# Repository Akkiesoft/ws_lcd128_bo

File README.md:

# Breakout boards for WaveShare RP2040-LCD-1.28

WaveShare RP2040-LCD-1.28のGPIOポートを利用した各種基板データ置き場です。

[GPIOの配置などはWaveShareのWikiを参照してください。](https://www.waveshare.com/wiki/RP2040-LCD-1.28)

* データ作成環境
    * KiCad 9.0.4
* 基板発注方法
    * のにそちしで基板のガーバーデータ、ドリルデータを生成します
    * JLCPCBなどで発注します
        * 基板の厚みは1.2mm程度もあれば十分です

## ブレイクアウトボード(board-breakout)

1.27mmピッチのGPIOピンを2.54mmピットに変換するブレイクアウトです。適当に空けた2.6mmの穴3つ付き。

基板1枚あたりに必要な部材は以下のとおりです。

* このデータから作成した基板 1枚
* 2x10 1.27mmピンヘッダー 2つ
* 2x10 2.54mmピンヘッダーもしくはピンソケット 2つ

## WIZnetチップ搭載Ethernetモジュール変換ボード(board-w5500)

RP2040-LCD-1.28にWIZnetチップ搭載Ethernetモジュールを搭載するための変換ボードです。

基板1枚あたりに必要な部材は以下のとおりです。

* このデータから作成した基板 1枚
* 2x10 1.27mmピンヘッダー 2つ
* WIZnetチップ搭載Ethernetモジュール
* お好みでロープロファイルピンヘッダー・ピンソケットの1x6を2つずつ
    * Ethernetモジュールのピンヘッダーは除去して付け替えます
    * 全体高を減らせます

GPIO配置は以下のとおりです。

* GP16: MI
* GP17: CSn
* GP18: SCK
* GP19: MO
* GP20: RST

## ライセンス / License

MIT License

2025 Akkiesoft

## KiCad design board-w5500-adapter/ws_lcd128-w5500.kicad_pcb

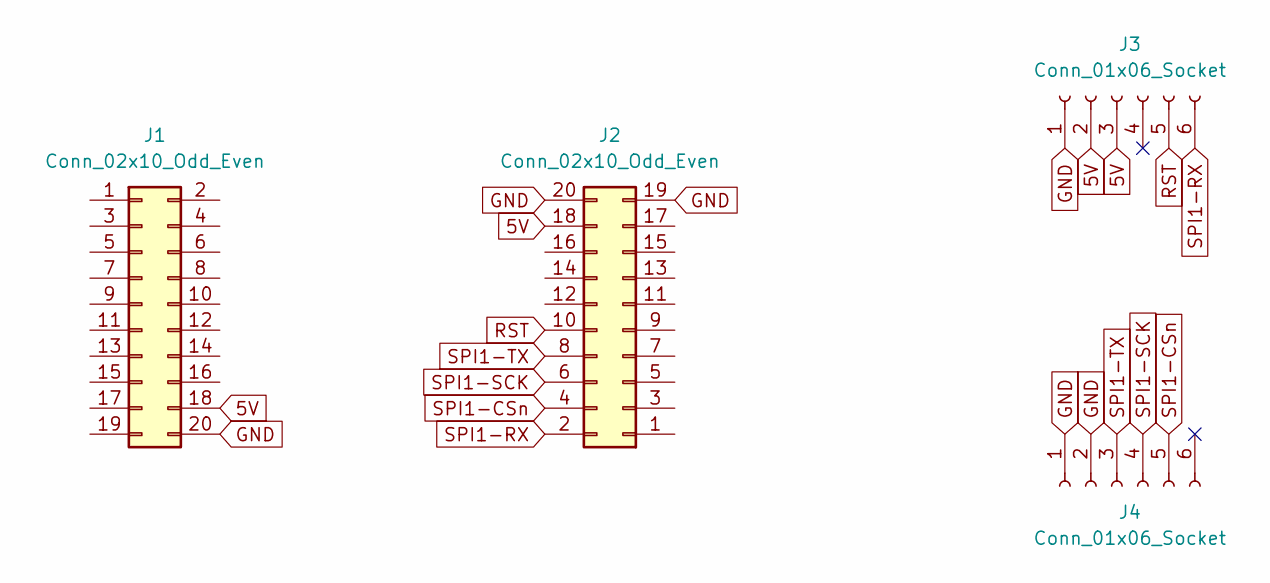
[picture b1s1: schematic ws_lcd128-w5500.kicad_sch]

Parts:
J1, J2: Conn_02x10_Odd_Even; PinHeader_2x10_P1.27mm_Vertical
J3, J4: Conn_01x06_Socket; PinHeader_1x06_P2.54mm_Vertical

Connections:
5V: J1.18, J2.18, J3.2, J3.3
GND: J1.20, J2.19, J2.20, J3.1, J4.1, J4.2
RST: J2.10, J3.5
SPI1-CSn: J2.4, J4.5
SPI1-RX: J2.2, J3.6
SPI1-SCK: J2.6, J4.4
SPI1-TX: J2.8, J4.3

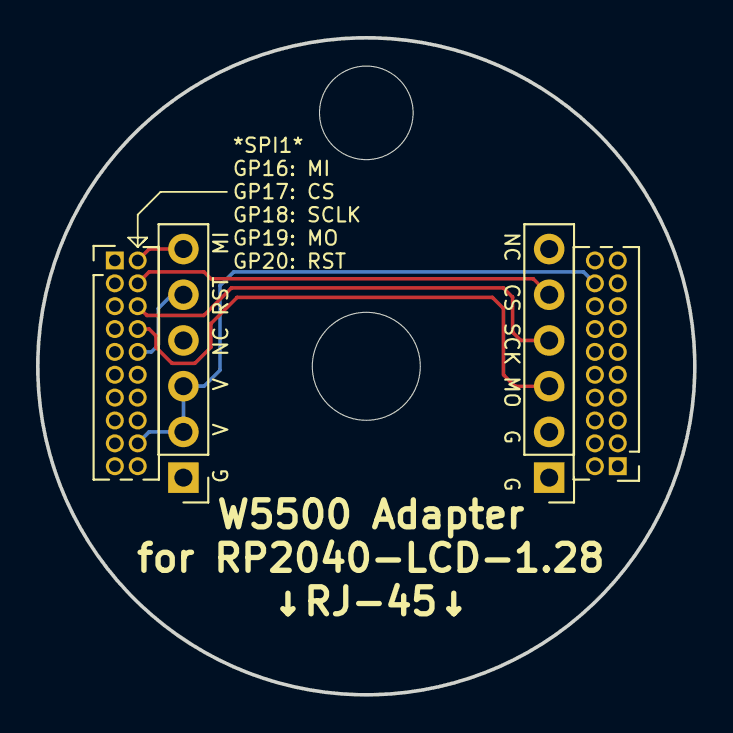
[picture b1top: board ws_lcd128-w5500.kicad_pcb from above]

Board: 2 copper layers, 36.5 x 36.5 mm, 4 parts (0 on the bottom side), 7 nets.

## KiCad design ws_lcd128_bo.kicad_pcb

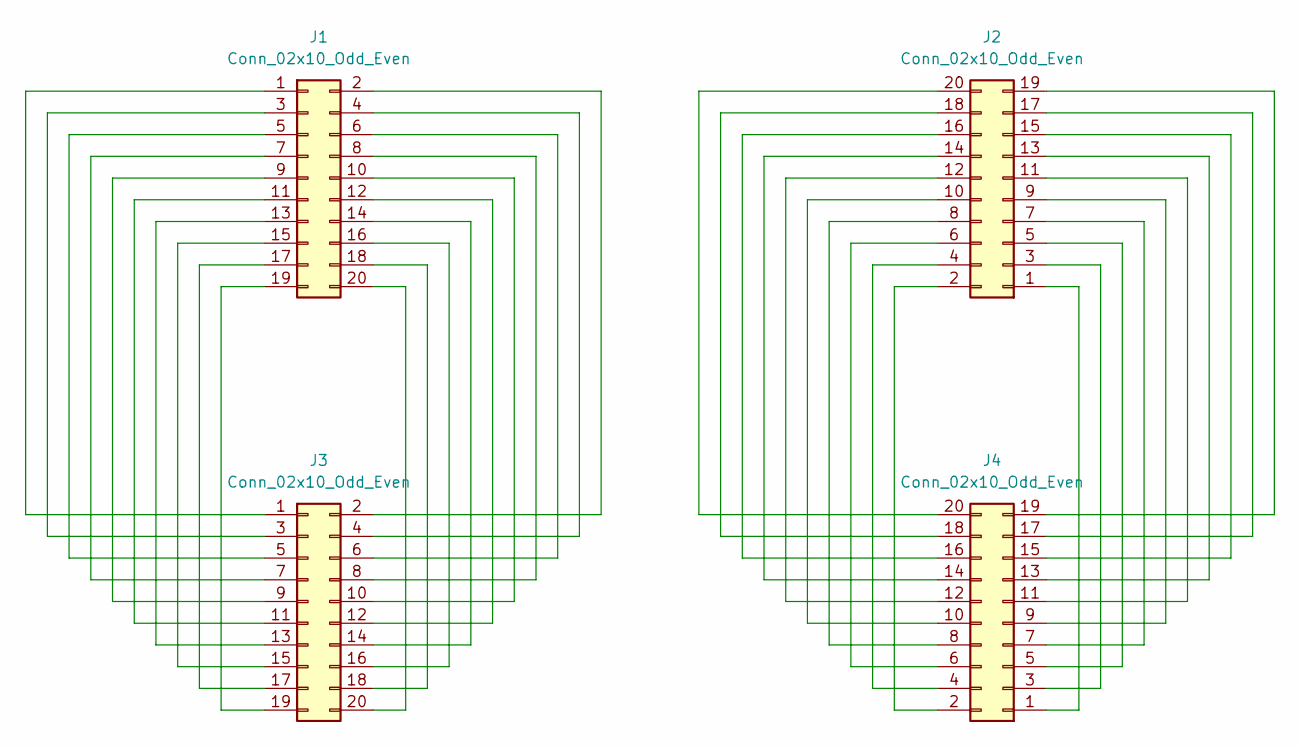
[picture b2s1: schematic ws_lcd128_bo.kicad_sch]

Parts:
J1, J2: Conn_02x10_Odd_Even; PinHeader_2x10_P1.27mm_Vertical
J3, J4: Conn_02x10_Odd_Even; PinHeader_2x10_P2.54mm_Vertical

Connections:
unnamed: J1.1, J3.1
unnamed: J1.2, J3.2
unnamed: J1.3, J3.3
unnamed: J1.4, J3.4
unnamed: J1.5, J3.5
unnamed: J1.6, J3.6
unnamed: J1.7, J3.7
unnamed: J1.8, J3.8
unnamed: J1.9, J3.9
unnamed: J1.10, J3.10
unnamed: J1.11, J3.11
unnamed: J1.12, J3.12
unnamed: J1.13, J3.13
unnamed: J1.14, J3.14
unnamed: J1.15, J3.15
unnamed: J1.16, J3.16
unnamed: J1.17, J3.17
unnamed: J1.18, J3.18
unnamed: J1.19, J3.19
unnamed: J1.20, J3.20
unnamed: J2.1, J4.1
unnamed: J2.2, J4.2
unnamed: J2.3, J4.3
unnamed: J2.4, J4.4
unnamed: J2.5, J4.5
unnamed: J2.6, J4.6
unnamed: J2.7, J4.7
unnamed: J2.8, J4.8
unnamed: J2.9, J4.9
unnamed: J2.10, J4.10
unnamed: J2.11, J4.11
unnamed: J2.12, J4.12
unnamed: J2.13, J4.13
unnamed: J2.14, J4.14
unnamed: J2.15, J4.15
unnamed: J2.16, J4.16
unnamed: J2.17, J4.17
unnamed: J2.18, J4.18
unnamed: J2.19, J4.19
unnamed: J2.20, J4.20

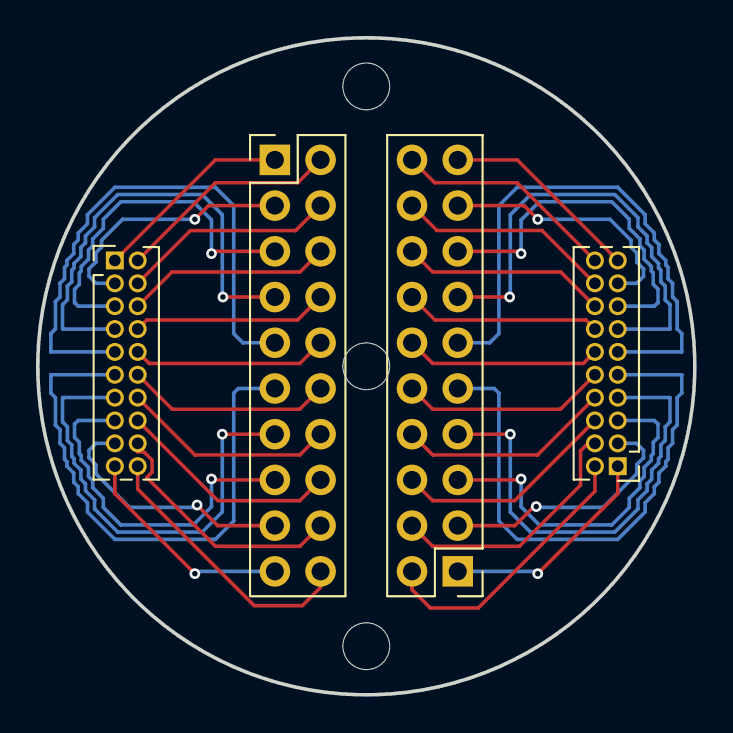
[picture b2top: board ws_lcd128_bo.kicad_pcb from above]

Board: 2 copper layers, 36.5 x 36.5 mm, 4 parts (0 on the bottom side), 40 nets.

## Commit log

2025-08-26 init
2025-08-26 code init
2025-08-26 README
2025-09-13 add w5500 adapter
